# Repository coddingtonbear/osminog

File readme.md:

# Octoprint-3D Printer Extras (Osminog)

I have a 3D printer managed by Octoprint in my basement and would rather
that I be able to turn on/off the fan and LED lighting supporting
that printer programmatically via Octoprint's events API.

What this provides is a USB device allowing me to:

* Turn the power outlet supporting the LED lighting and 3D printer
  off or on.
* Switch DC power to a LED lighting strip.
* Gather temperature and humidity measurements.
* Watch whether I'm nearly out of filament using a [cheap filament sensor off of Ebay](https://www.ebay.com/i/371913487805?chn=ps&dispItem=1).
* Beep when paused or when a print has completed.  This is useful for knowing when to change filament or when I need to insert a captive bolt or magnet.

## Commands

* ``POWERON``: Turn on the RF-controlled outlet
* ``POWEROFF``: Turn off the RF-controlled outlet
* ``GETTEMPERATURE``: Return the current temperature (Celsius)
* ``GETHUMIDITY``: Return the current humidity level
* ``BUZZER``: Buzz the buzzer for half a second
* ``FILAMENT``: Return a "1" or "0" depending upon whether filament is detected in the filament sensor.

## Schematic

## Errata

* In the photo above of the final board, you'll see two bodges; those are there
  to support programming the device via the USB port.  In the uploaded
  schematics, the board has been corrected to include that resistor and
  capacitor.

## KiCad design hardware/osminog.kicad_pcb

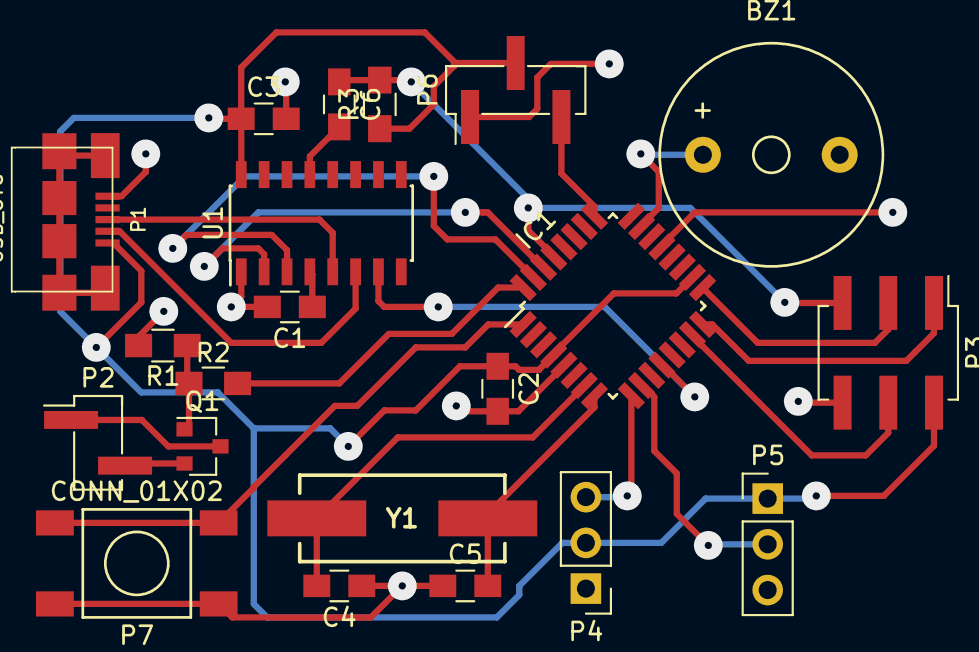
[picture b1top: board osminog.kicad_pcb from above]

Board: 2 copper layers, 21 parts (0 on the bottom side), 24 nets.

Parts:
BZ1: Buzzer; Buzzer_12x9.5RM7.6
C1, C2, C3, C6: 0.1u; C_0805_HandSoldering
C4, C5: 22p; C_0805_HandSoldering
IC1: ATMEGA328PB-A; TQFP-32_7x7mm_Pitch0.8mm
P1: USB_OTG; MICRO-B_USB-INVERTED
P2: CONN_01X02; Pin_Header_Straight_1x02_Pitch2.54mm_SMD_Pin1Left
P3: CONN_02X03; Pin_Header_Straight_2x03_Pitch2.54mm_SMD
P4, P5: CONN_01X03; Pin_Header_Straight_1x03_Pitch2.54mm
P6: CONN_01X03; Pin_Header_Straight_1x03_Pitch2.54mm_SMD_Pin1Left
P7: CONN_01X02; SWITCH_FSM_JSM_off-mom
Q1: BSS138; SOT-23
R1, R3: 10k; R_0805_HandSoldering
R2: 470; R_0805_HandSoldering
U1: CH340G; SOIC-16_3.9x9.9mm_Pitch1.27mm
Y1: 12; HC-49S

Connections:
+5V: C2.1, C3.1, IC1.4, IC1.18, P1.1, P3.2, P4.2, P5.1, P6.2, R3.1, U1.16
BUZZER: BZ1.1, IC1.23
CLKOUT: IC1.12, U1.7
ENABLE_RELAY: IC1.32, R2.2
GND: BZ1.2, C1.2, C2.2, C3.2, C4.1, C5.1, IC1.5, IC1.21, P1.5, P3.6, P4.1, P5.3, P6.1, P7.2, R1.2, U1.1
LED: IC1.25, P6.3
MISO: IC1.16, P3.1
MOSI: IC1.15, P3.4
unnamed: C1.1, U1.4
unnamed: C4.2, IC1.7, Y1.1
unnamed: C5.2, IC1.8, Y1.2
unnamed: C6.2, U1.13
unnamed: IC1.30, U1.2
unnamed: IC1.31, U1.3
unnamed: P1.2, U1.6
unnamed: P1.3, U1.5
unnamed: P2.1, Q1.3
unnamed: P2.2, Q1.2
unnamed: Q1.1, R1.1, R2.1
RESET: C6.1, IC1.29, P3.5, R3.2
SCK: IC1.17, P3.3
SWITCH: IC1.1, P7.1
TEMP: IC1.10, P5.2
XMIT: IC1.9, P4.3

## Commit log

2017-03-16 And so it begins...
2017-03-19 Updating to use ATMEGA328pb...at less than 2USD, I might as well.
2017-03-27 Adding latest version of osminog.
2017-03-27 Updating readme to include photo and schematic.
2017-03-27 Updating schematic to include some missing values.
2017-08-07 Adding initial version of Osminog.
2017-08-07 Renaming package.
2017-08-07 Adding some logging messages.
2017-08-07 Fixing setup.
2017-08-07 Hook to poweroff/poweron instead of print stopped/started.
2017-08-07 Only write if a serial connection was established.
2017-08-07 Properly setting port values; more logging messages.
2017-08-08 Reconnect on settings change.
2017-08-08 Flush input buffer before sending command.
2017-08-08 Send a newline afterward.
2017-08-08 Allow two seconds for a reply.
2017-08-08 Send crlf.
2017-08-08 Better connection and pause handling.
2017-08-08 Removing an unnecessary set.
2017-08-08 Adding filament sensor commands.
2017-08-08 Proper reconnection handling.
2017-08-08 Typo.
2017-08-08 Better reconnect handling; require two sequential filament check failures.
2017-08-08 Updating readme to reflect new changes.
2017-08-08 Also beep if the print completed normally.
2017-08-08 Updating readme to be a little clearer.
2017-08-08 Relabeling 'LED' to 'FILAMENT' to describe that pins current function.
2017-08-08 Fixing logging messages.
2017-08-30 Do not bother with gathering multiple filament check results.
2017-08-30 Check twice, though.
2017-09-04 Announce version number on start.
2017-09-04 Slightly more robust handling of beeps and buzzes.
2017-09-04 Support earlier versions of PySerial.
